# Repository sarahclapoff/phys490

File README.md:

# phys490
Physics 490 - Advanced Electronics
Spring 2022

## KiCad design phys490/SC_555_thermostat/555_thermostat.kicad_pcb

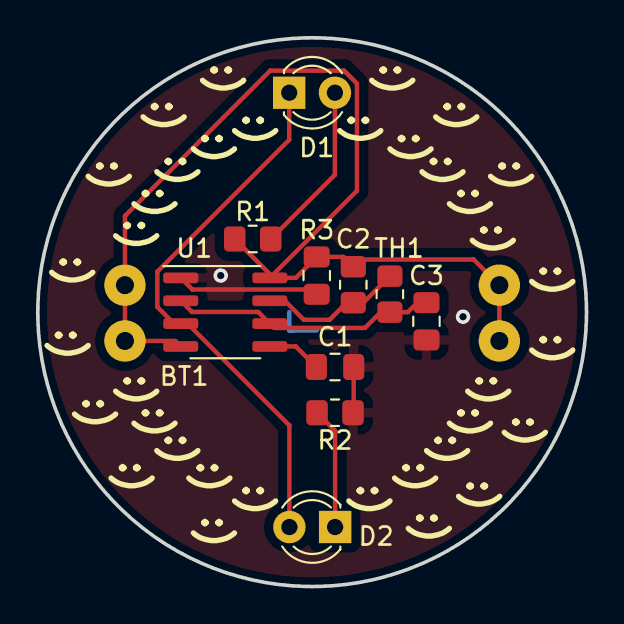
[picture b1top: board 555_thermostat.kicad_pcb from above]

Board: 2 copper layers, 30.5 x 30.5 mm, 11 parts (0 on the bottom side), 8 nets.

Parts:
BT1: baby_batt; coinbat
C1: 10n; C_0805_2012Metric_Pad1.18x1.45mm_HandSolder
C2: 0.1; C_0805_2012Metric_Pad1.18x1.45mm_HandSolder
C3: 33micro; C_0805_2012Metric_Pad1.18x1.45mm_HandSolder
D1, D2: LED; LED_D3.0mm
R1, R2: 470; R_0805_2012Metric_Pad1.20x1.40mm_HandSolder
R3: 4k; R_0805_2012Metric_Pad1.20x1.40mm_HandSolder
TH1: 4.7k/25C; R_0805_2012Metric_Pad1.20x1.40mm_HandSolder
U1: my555; SOIC-8_3.9x4.9mm_P1.27mm

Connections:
+3V0: BT1.1 (Va), BT1.2 (Vb), BT1.3 (Vc), BT1.4 (Vd), C2.1, R1.1, R3.2, U1.4 (RST), U1.8 (Vdd)
GND: BT1.5 (G), C1.2, C2.2, C3.2, R2.2, U1.1 (GND)
unnamed: C1.1, U1.5 (CONT)
unnamed: D1.1 (K), D2.2 (A), U1.3 (OUT)
unnamed: D1.2 (A), R1.2
unnamed: D2.1 (K), R2.1
unnamed: R3.1, TH1.1, U1.7 (DSCH)
trg: C3.1, TH1.2, U1.2 (TRG), U1.6 (TRSH)
